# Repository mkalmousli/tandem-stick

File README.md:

<p align="center">
<a href="https://mkalmousli.github.io/tandem-stick/"><b>See how it works →</b></a> ·
<a href="https://mkalmousli.github.io/tandem-stick/#/explore">Explore in 3D</a> ·
<a href="https://mkalmousli.github.io/tandem-stick/#/downloads">Downloads</a>
</p>

Open hardware DIY project: a button-free USB stick that pairs with other sticks by radio, so one host controls many machines. One stick per target, one for you.

**Status: untested DIY design.** The board passes design-rule checks and the case is printable, but nothing has been built or tested on hardware. Firmware is coming later.

**Site:** https://mkalmousli.github.io/tandem-stick/

Three pages and a GitHub link:

| Page | What it has |
|---|---|
| Home | Scroll presentation: how it works, a live 3D demo with five real-life scenarios, use cases, host vs target, FAQ |
| Explore | The main thing. 3D viewer with tabs for Tour, Parts, Signal, Guide (drawings, pinout, build, print, plan) and Files (every file previewed: board from the Gerbers, case STL in 3D, BOM and placement tables, source) |
| Downloads | Bundles and files with SHA-256 checksums you can verify in the browser |

## Repository

    web/          static site: one index.html, all UI in plain scripts under web/js (three.js r160 vendored)
    hardware/     KiCad board generated by build_board.py, DRC script, fab outputs
    mechanical/   printable case STLs and their generator
    scripts/      build-site.mjs assembles dist/ with bundles and checksums
    tests/        node:test suite for the design data, board files and site scripts

## Develop

    npm test           # design checks
    npm run serve      # build dist/ and open http://localhost:8765

Needs Node 20+ and the `zip` command. Serve the site over HTTP rather than opening it from `file://`.

## Caveats

- Part numbers are candidate families; verify datasheets and stock before ordering.
- Costs are rough estimates, not quotes.
- No ESD diode, no schematic or ERC yet; see Explore → Guide → Roadmap and risks.

Licence: MIT. Three.js is MIT, see `web/explorer/vendor/LICENSE-three`.

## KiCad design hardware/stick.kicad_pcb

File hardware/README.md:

# Tandem Stick: board

KiCad 7 board generated by `build_board.py` (pcbnew API): `python3 build_board.py && python3 drc.py report.txt`.

- 33 × 17.4 mm main board plus a 13.5 mm USB-A tab (46.5 mm overall), 4 layers (signal, GND, 3V3, GND), 1.6 mm.
- `fab/gerbers/` Gerbers and drill, `fab/bom.csv`, `fab/pos.csv` for assembly. J1 is the board's own USB-A tab and TP1/TP2 are test pads, so none of them are in the BOM. Order ENIG (gold) finish for the plug pads.
- Fill the LCSC column and confirm stock and rotation offsets in the fab's preview before ordering.

## Flash
Short TP1 (BOOT) to TP2 (GND) while plugging in, then flash over USB (ESP32-S3 native USB).

## Known limits (not tested on hardware)
- DRC: 0 unconnected pads; only library-path and courtyard warnings remain (C1, C2 and U2 courtyards touch). No schematic or ERC; nets are in `build_board.py`.
- No ESD diode (planned for the respin). C3 (100 nF) sits on the back side under the module power pads, connected by via-in-pad: ask the fab for filled or tented vias, or accept the small solder-wicking risk.
- LED runs from 3.3 V and may be dim.
- Antenna end (x < 5.9 mm) is keepout on all layers; keep the case and your hand away from it.
- First article may need a respin. Order the minimum quantity first.

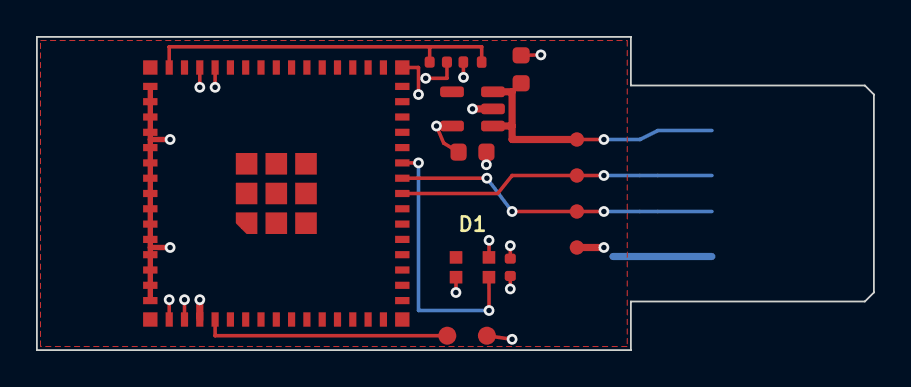
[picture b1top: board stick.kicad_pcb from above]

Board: 4 copper layers, 46.5 x 17.4 mm, 12 parts (1 on the bottom side), 8 nets.

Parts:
C1, C2: 10uF; C_0603_1608Metric
C3, C4: 100nF; C_0402_1005Metric
C5: 1uF; C_0402_1005Metric
D1: WS2812B-2020; LED_WS2812B-2020_PLCC4_2.0x2.0mm
J1: USB-A edge plug
R1: 10k; R_0402_1005Metric
TP1: BOOT; TestPoint_Pad_D1.0mm
TP2: GND; TestPoint_Pad_D1.0mm
U1: ESP32-S3-MINI-1-N4; ESP32-S3-MINI-1
U2: AP2112K-3.3; SOT-23-5

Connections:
3V3: C2.1, C3.2, C4.1, D1.4, R1.1, U1.3, U2.5
EN: C5.1, R1.2, U1.45
GND: C1.2, C2.2, C3.1, C4.2, C5.2, D1.2, J1.4, J1.T4, TP2.1, U1.1, U1.2, U1.42, U1.43, U1.46, U1.47, U1.48, U1.49, U1.50, U1.51, U1.52, U1.53, U1.54, U1.55, U1.56, U1.57, U1.58, U1.59, U1.60, U1.61, U1.62, U1.63, U1.64, U1.65, U2.2
IO0: TP1.1, U1.4
LED_DIN: D1.3, U1.25
USB_DM: J1.2, J1.T2, U1.23
USB_DP: J1.3, J1.T3, U1.24
VBUS: C1.1, J1.1, J1.T1, U2.1, U2.3

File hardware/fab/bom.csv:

Comment,Designator,Footprint,MPN,LCSC
ESP32-S3-MINI-1-N4,U1,ESP32-S3-MINI-1,ESP32-S3-MINI-1-N4,
AP2112K-3.3,U2,SOT-23-5,AP2112K-3.3TRG1,
WS2812B-2020,D1,LED_WS2812B-2020,WS2812B-2020,
10uF,"C1,C2",C_0603,,
1uF,C5,C_0402,,
100nF,"C3,C4",C_0402,,
10k,R1,R_0402,,

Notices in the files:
README.md:
License: MIT
